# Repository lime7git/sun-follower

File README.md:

# sun-follower
 Academical project of sun follower based on Raspberry Pi Pico.

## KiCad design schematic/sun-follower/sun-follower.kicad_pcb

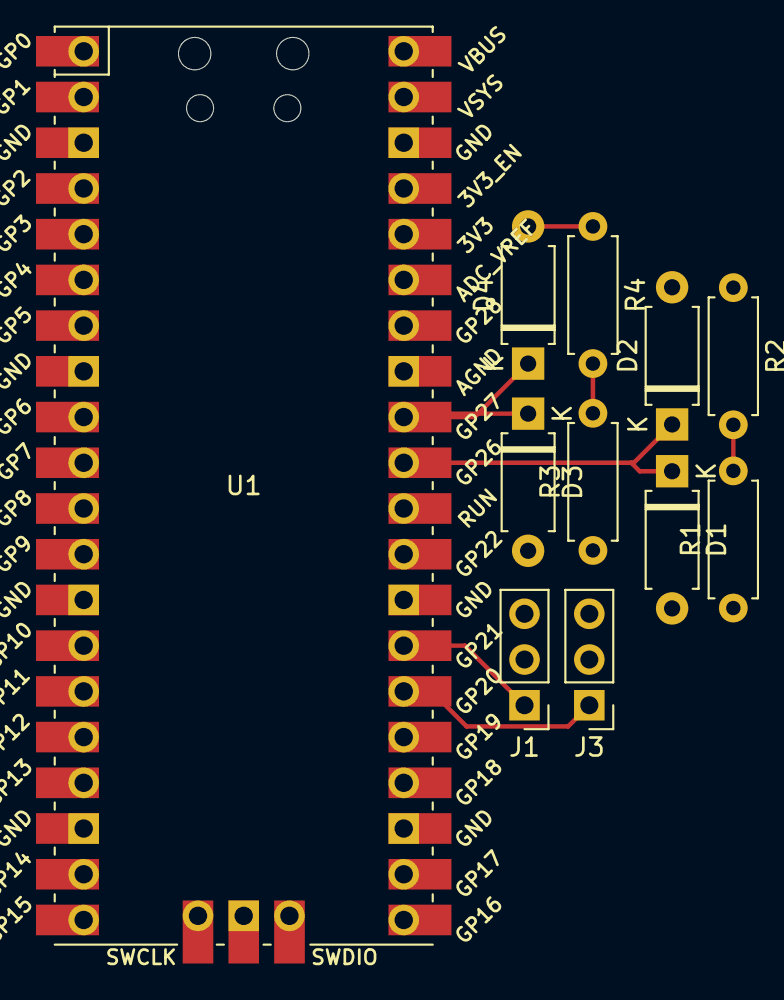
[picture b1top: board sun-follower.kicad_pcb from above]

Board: 2 copper layers, 11 parts (0 on the bottom side), 10 nets.

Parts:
D1, D2, D3, D4: 1N4148; D_A-405_P7.62mm_Horizontal
J1, J3: SERWO_1; PinHeader_1x03_P2.54mm_Vertical
R1, R2, R3, R4: R; R_Axial_DIN0207_L6.3mm_D2.5mm_P7.62mm_Horizontal
U1: Pico; RPi_Pico_SMD_TH

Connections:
+5V: J1.2, J3.2
ADC_0: D1.1, D2.1, U1.31
ADC_1: D3.1, D4.1, U1.32
GND: J1.3, J3.3, R1.2, R2.2, R3.2, R4.2, U1.3, U1.8, U1.13, U1.18, U1.23, U1.28, U1.33, U1.38, U1.42
unnamed: D1.2, R1.1
unnamed: D2.2, R2.1
unnamed: D3.2, R3.1
unnamed: D4.2, R4.1
PWM1: J1.1, U1.27
PWM2: J3.1, U1.26

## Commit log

2021-11-03 adding test_git.txt
    test
2021-11-04 Add some changes
2021-11-08 Added some changes
2021-11-08 Redesign
2021-11-08 Design of electronic case
2021-11-08 Adding whole for digital voltometer
2021-11-08 Added voltometer
2021-11-08 Final ver. 1.0
2021-11-09 Added some new 3D models
2021-11-10 Servo cases and cable holders + some small stuff
2021-11-12 Added new bottom servo and its holders, done some small fixes
2021-11-16 Adding Docs
2021-11-16 Change location
2021-11-16 Small changes
2021-11-17 teoria_rodzial
2021-12-02 Added STL files to 3D printing
2021-12-02 Change wires holders
2021-12-02 Added all stl files
2021-12-02 Small edits
2021-12-16 Fixses
2021-12-18 Edit
2021-12-21 Some case changes
2022-01-19 schematic
2022-01-26 soft_following x y v.1
2022-01-26 update_soft
2022-01-28 sesja
2022-01-31 render
2022-01-31 Projekt update
2022-01-31 serwo doc
2022-02-01 update_docs
2022-02-02 gitignore
    Update gitignore to ignore word temp. and backup files.
2022-02-02 do_sprawdzenia
    complete ;-)
2022-02-02 convert_to_pdf
2022-02-03 corrections_of_project
    to print
2022-02-08 Project final
